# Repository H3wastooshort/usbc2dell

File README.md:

# USB-C to DELL
An adapter to allow charging Laptops equipped with legacy connectors via USB Type-C.

## Why make my own?

I could just slap together a USB-C PD trigger-board and a cut-off end of a cable and call it a day, but that would cause two problems:
 - the laptop won't charge because it's not seeing an ID chip
 - even if it does use the power supply, it might draw too much current if connected to for example a 45W USB-C power supply.

This project remidies this, by negotiating USB PD and then emulating an ID chip with the same parameters as read from the USB-C power supply. Using a 45W USB-C power supply, the laptop will know that it's only capable of 45W.

## Schematic

## PCB

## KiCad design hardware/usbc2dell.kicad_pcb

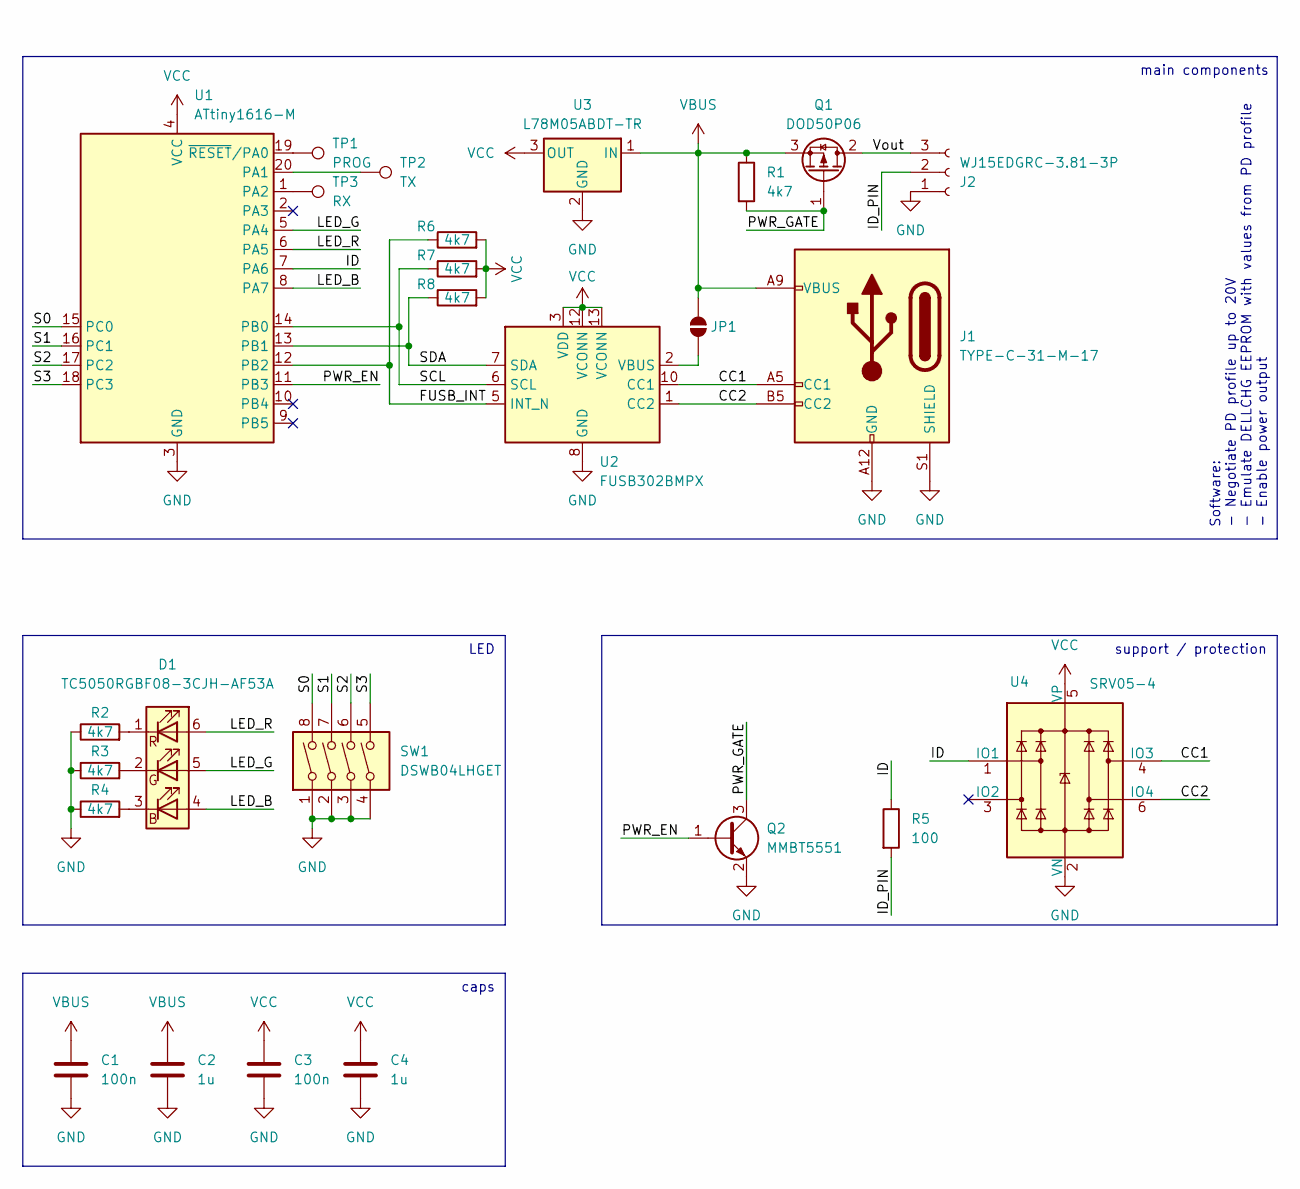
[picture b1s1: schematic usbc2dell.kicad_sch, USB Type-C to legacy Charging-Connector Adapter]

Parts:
C1, C3: 100n; C_0603_1608Metric; LCSC C14663
C2, C4: 1u; C_0603_1608Metric; LCSC C15849
D1: TC5050RGBF08-3CJH-AF53A; LED_RGB_5050-6; LCSC C784540
J1: TYPE-C-31-M-17; USB_C_Receptacle_HRO_TYPE-C-31-M-17; LCSC C283540
J2: WJ15EDGRC-3.81-3P; PhoenixContact_MC_1,5_3-G-3.81_1x03_P3.81mm_Horizontal; LCSC C8406
JP1: SolderJumper_2_Open; SolderJumper-2_P1.3mm_Open_TrianglePad1.0x1.5mm
Q1: DOD50P06; TO-252-3_TabPin2; LCSC C41430590
Q2: MMBT5551; SOT-23; LCSC C2145
R1, R2, R3, R4, R6, R7, R8: 4k7; R_0603_1608Metric; LCSC C23162
R5: 100; R_0603_1608Metric; LCSC C22775
SW1: DSWB04LHGET; SW_DIP_SPSTx04_Slide_9.78x12.34mm_W7.62mm_P2.54mm; LCSC C99418
TP1: PROG; TestPoint_Pad_D2.0mm
TP2: TX; TestPoint_Pad_D2.0mm
TP3: RX; TestPoint_Pad_D2.0mm
U1: ATtiny1616-M; VQFN-20-1EP_3x3mm_P0.4mm_EP1.7x1.7mm
U2: FUSB302BMPX; WQFN-14-1EP_2.5x2.5mm_P0.5mm_EP1.45x1.45mm; LCSC C442699
U3: L78M05ABDT-TR; TO-252-3_TabPin2; LCSC C58069
U4: SRV05-4; SOT-23-6; LCSC C20615829

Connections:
/CC1: J1.A5 (CC1), U2.10 (CC1), U2.11 (CC1), U4.4 (IO3)
/CC2: J1.B5 (CC2), U2.1 (CC2), U2.14 (CC2), U4.6 (IO4)
/FUSB_INT: R6.1, U1.12 (PB2), U2.5 (INT_N)
/ID: R5.1, U1.7 (PA6), U4.1 (IO1)
/ID_PIN: J2.2, R5.2
/LED_B: D1.4 (BA), U1.8 (PA7)
/LED_G: D1.5 (GA), U1.5 (PA4)
/LED_R: D1.6 (RA), U1.6 (PA5)
/PWR_EN: Q2.1 (B), U1.11 (PB3)
/PWR_GATE: Q1.1 (G), Q2.3 (C), R1.2
/S0: SW1.8, U1.15 (PC0)
/S1: SW1.7, U1.16 (PC1)
/S2: SW1.6, U1.17 (PC2)
/S3: SW1.5, U1.18 (PC3)
/SCL: R7.1, U1.14 (PB0), U2.6 (SCL)
/SDA: R8.1, U1.13 (PB1), U2.7 (SDA)
/Vout: J2.3, Q1.2 (D)
GND: C1.2, C2.2, C3.2, C4.2, J1.A12 (GND), J1.B12 (GND), J1.S1 (SHIELD), J2.1, Q2.2 (E), R2.1, R3.1, R4.1, SW1.1, SW1.2, SW1.3, SW1.4, U1.3 (GND), U1.21 (GND), U2.8 (GND), U2.9 (GND), U2.15 (GND), U3.2 (GND), U4.2 (VN)
unnamed: D1.3 (BK), R4.2
unnamed: D1.2 (GK), R3.2
unnamed: D1.1 (RK), R2.2
unnamed: JP1.1 (A), U2.2 (VBUS)
unnamed: TP2.1, U1.20 (PA1)
unnamed: TP3.1, U1.1 (PA2)
unnamed: TP1.1, U1.19 (~RESET/PA0)
VBUS: C1.1, C2.1, J1.A9 (VBUS), J1.B9 (VBUS), JP1.2 (B), Q1.3 (S), R1.1, U3.1 (IN)
VCC: C3.1, C4.1, R6.2, R7.2, R8.2, U1.4 (VCC), U2.3 (VDD), U2.4 (VDD), U2.12 (VCONN), U2.13 (VCONN), U3.3 (OUT), U4.5 (VP)

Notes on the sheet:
caps
Software: - Negotiate PD profile up to 20V - Emulate DELLCHG EEPROM with values from PD profile - Enable power output
LED
support / protection
main components

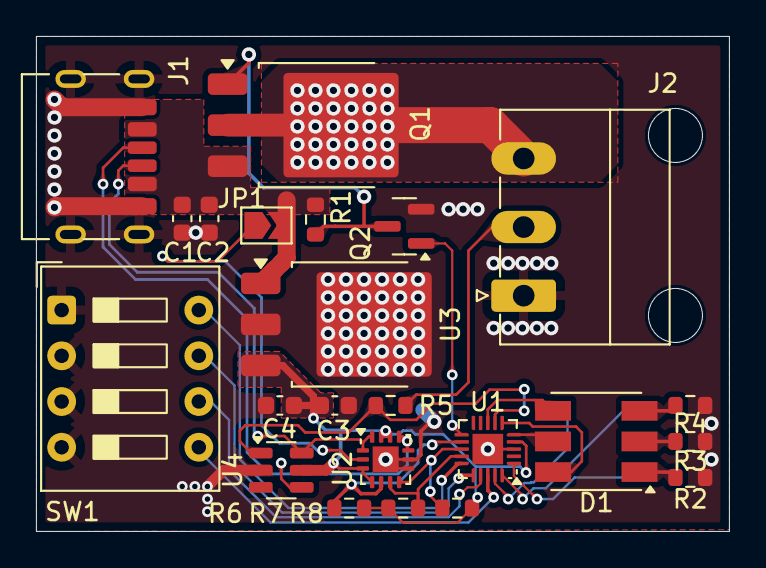
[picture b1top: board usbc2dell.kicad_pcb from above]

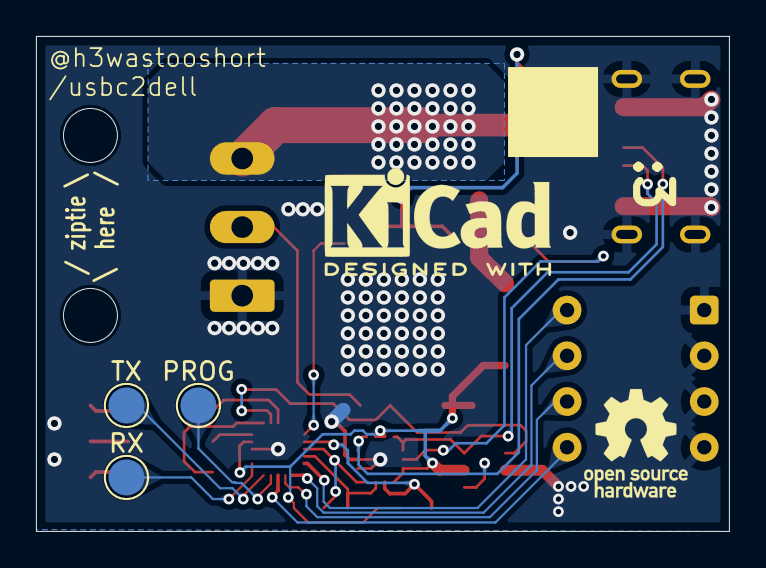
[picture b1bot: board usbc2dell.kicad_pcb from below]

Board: 2 copper layers, 38.5 x 27.5 mm, 30 parts (5 on the bottom side), 27 nets.

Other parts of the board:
HOLE1, HOLE2: MountingHole_3mm
ICON1: OSHW-Logo_5.7x6mm_SilkScreen
ICON2: KiCad-Logo2_5mm_SilkScreen

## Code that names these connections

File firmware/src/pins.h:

#pragma once
#include <Arduino.h>

const uint8_t PIN_ID = PIN_PB4;

const uint8_t PIN_FUSB_INT = PIN_PB2;

const uint8_t PIN_PWR_EN = PIN_PB3;

//LED
const uint8_t PIN_LED_R = PIN_PA5;
const uint8_t PIN_LED_G = PIN_PA6;
const uint8_t PIN_LED_B = PIN_PA7;

//DIP Switchesa
const uint8_t PIN_SW_EMU_TYPE_0 = PIN_PC0;
const uint8_t PIN_SW_EMU_TYPE_1 = PIN_PC1;
const uint8_t PIN_SW_USE_PPS = PIN_PC2;
const uint8_t PIN_SW_LED_BRIGHT = PIN_PC3;



//automatic, ignore
constexpr uint8_t PINS_LED[3] = {PIN_LED_R,PIN_LED_G,PIN_LED_B};

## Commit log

2025-04-01 rough schematic
2025-04-01 add config switchbank
2025-04-03 add bjt to drive mosfet
2025-04-03 dell emu class outline
2025-04-04 work on stuff
2025-04-04 fix dell_chg_emu class very silly mistake
2025-04-04 fix another very silly mistake
2025-04-04 try to fix upcast
2025-04-04 rough PCB layout
2025-04-04 slightly miserable trace routing
2025-04-05 add ziptie-holes
2025-04-05 github actions thingie
2025-04-05 move hw files
2025-04-05 update action to kicad9
2025-04-05 added sort-of correct 3d models instead of none at all
2025-04-05 improve silkscreen
2025-04-06 add caps
2025-04-06 use pullup-resistors as transistor resistor
2025-04-06 prod?
2025-04-06 more GND vias
2025-04-06 silkscreen
2025-04-07 parts sel
2025-04-07 change ESD diodes
2025-04-07 silk
2025-04-07 move PCB
2025-04-07 add teardrops
2025-04-07 partsel
2025-04-07 switch to phoenix-style connectors
2025-04-08 fix MOSFET
2025-04-08 fix mosfet 2
2025-04-08 stuff
2025-04-10 forgot to commit, now don't remember what i did
2025-04-10 nicer traces + mosfet still fucked
2025-04-10 attempt to fix mosfet
2025-04-10 actually fix mosfet
2025-04-11 ledcolors 2
2025-04-11 #pragma once it builds now, yay :)
2025-04-11 LED dimming
2025-04-11 correct 7805 part num
2025-04-11 thermals
2025-04-11 layout changes, thermals + ampacity
2025-04-11 comp sel
2025-05-08 put ID pin on pin with DAC capability for possible analog comms in future
2026-01-24 [FW] mark chg_emu_c as pure virtual
2026-01-24 [FW] fix emulator selection
2026-01-24 [FW] prevent instantiating base emu
2026-01-24 [FW] fix severe pointer misuse using a pointer to a value after leaving that contexts value is really bad! the freed memory will eventually be overwritten/corrupted!
2026-01-24 [FW] rename dell_emu functions
2026-01-24 [FW] properly initialize statemachine
2026-01-24 [FW] use correct type for emuselect
2026-02-01 [PCB] fix pullups
2026-02-01 [PCB] move stuff
2026-02-01 [PCB] at JLCPCB serialnumber QR code position
2026-02-01 [PCB] idk
2026-02-19 [FW] clean up code
2026-02-19 [FW] change header filenames
2026-02-19 [FW] trying to squeeze in a logger
